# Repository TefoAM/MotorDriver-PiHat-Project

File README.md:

# MotorDriver-PiHat-Project

The PiHAT is a hardware board attached to a Raspberry Pi microcontroller. it is used to drive a motor using an external power source.

##Bill of Materials

- boost convertor.asc
- foldbackcircuit.asc
- main power circuit.asc
- zener.cir
- H-Bridge circuit.asc
- LED Circuit.asc

##Instruction on how to use this repo

This repository contains all the files made using LT Spice and Kicad with which simulations to test the behaviors of the individual circuits were performed.

This git includes a list of documents created during the design of a motor driver PiHAT for a design project.
The software required to use these documents is LT Spice, whcih can be downloaded by following the link below.
https://www.analog.com/en/design-center/design-tools-and-calculators/ltspice-simulator.html# 

The zener.cir file needs to be added into spice as a component to be used. The simulation won't work without it.
Anyone can use these document files except they cannot distribute closed source versions.
- see license.

signed TefoAM

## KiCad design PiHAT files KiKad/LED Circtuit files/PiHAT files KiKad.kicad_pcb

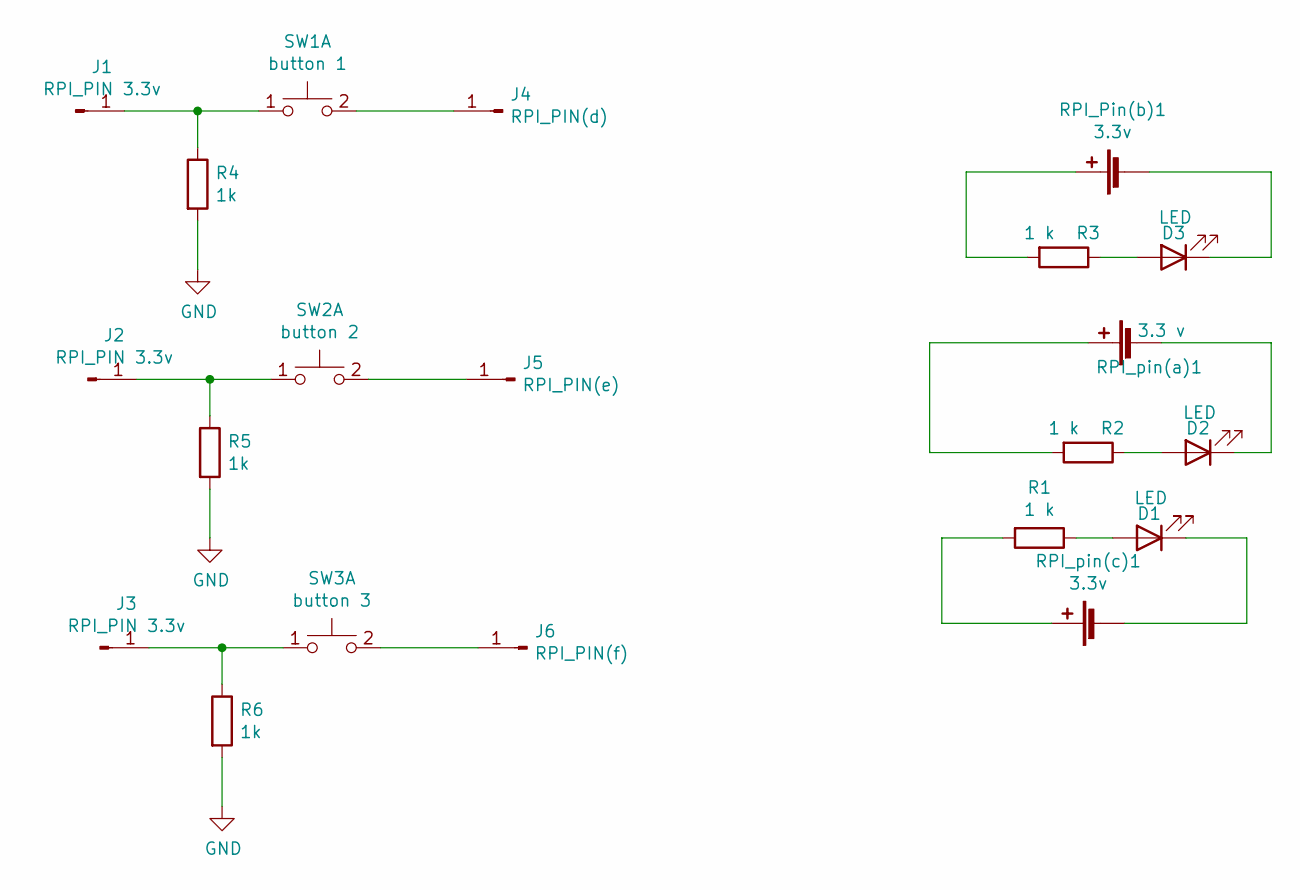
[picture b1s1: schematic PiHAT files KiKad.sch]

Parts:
D1, D2, D3: LED; LED_0603_1608Metric_Pad1.05x0.95mm_HandSolder
J1, J2, J3: RPI_PIN 3.3v; PinHeader_1x01_P2.54mm_Vertical
J4: RPI_PIN(d); PinHeader_1x01_P2.54mm_Vertical
J5: RPI_PIN(e); PinHeader_1x01_P2.54mm_Vertical
J6: RPI_PIN(f); PinHeader_1x01_P2.54mm_Vertical
R1, R2, R3: 1 k; R_0201_0603Metric
R4, R5, R6: 1k; R_0201_0603Metric
RPI_Pin(b)1: 3.3v; PinHeader_1x02_P2.54mm_Vertical
RPI_pin(a)1: 3.3 v; PinHeader_1x02_P2.54mm_Vertical
RPI_pin(c)1: 3.3v; PinHeader_1x02_P2.54mm_Vertical
SW1: button 1; SW_Push_1P1T_NO_6x6mm_H9.5mm
SW2: button 2; SW_Push_1P1T_NO_6x6mm_H9.5mm
SW3: button 3; SW_Push_1P1T_NO_6x6mm_H9.5mm

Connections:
GND: R4.2, R5.2, R6.2
unnamed: D1.1 (K), RPI_pin(c)1.2 (-)
unnamed: D1.2 (A), R1.1
unnamed: D2.1 (K), RPI_pin(a)1.2 (-)
unnamed: D2.2 (A), R2.1
unnamed: D3.1 (K), RPI_Pin(b)1.2 (-)
unnamed: D3.2 (A), R3.1
unnamed: J1.1, R4.1, SW1.1 (C)
unnamed: J2.1, R5.1, SW2.1 (C)
unnamed: J3.1, R6.1, SW3.1 (C)
unnamed: J4.1, SW1.2 (D)
unnamed: J5.1, SW2.2 (D)
unnamed: J6.1, SW3.2 (D)
unnamed: R1.2, RPI_pin(c)1.1 (+)
unnamed: R2.2, RPI_pin(a)1.1 (+)
unnamed: R3.2, RPI_Pin(b)1.1 (+)

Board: 2 copper layers, 21 parts (0 on the bottom side), 16 nets, no tracks yet.

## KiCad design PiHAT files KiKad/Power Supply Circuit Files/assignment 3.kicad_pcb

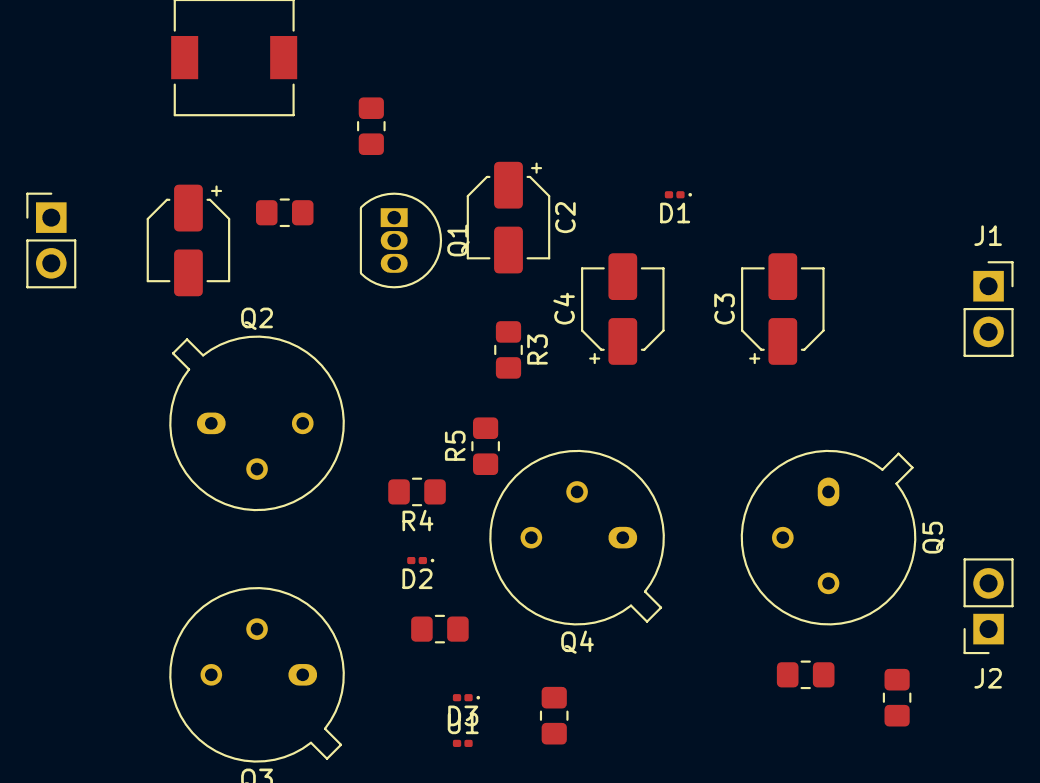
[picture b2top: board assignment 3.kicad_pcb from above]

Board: 4 copper layers, 26 parts (0 on the bottom side), 15 nets, no tracks yet.

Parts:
C1: 10p; CP_Elec_4x3
C2: 0.1u; CP_Elec_4x3
C3: 10u; CP_Elec_4x3
C4: 100u; CP_Elec_4x3
D1, D2, D3: 1N5817; D_0201_0603Metric
J1: Motor_voltage_input; PinSocket_1x02_P2.54mm_Vertical
J2: Controller_input_voltage; PinSocket_1x02_P2.54mm_Vertical
L1: 330u; L_6.3x6.3_H3
Q1: 2N3905; TO-92_Inline
Q2, Q3, Q4, Q5: 2N2219; TO-39-3
R1, R2, R6: 1000; R_0805_2012Metric_Pad1.20x1.40mm_HandSolder
R3: 47000; R_0805_2012Metric_Pad1.20x1.40mm_HandSolder
R4: 470; R_0805_2012Metric_Pad1.20x1.40mm_HandSolder
R5: 4; R_0805_2012Metric_Pad1.20x1.40mm_HandSolder
R7: 5; R_0805_2012Metric_Pad1.20x1.40mm_HandSolder
R8: 100000; R_0805_2012Metric_Pad1.20x1.40mm_HandSolder
R9: 8270; R_0805_2012Metric_Pad1.20x1.40mm_HandSolder
U1: OPAMP; R_0201_0603Metric
power_supply_input1: 12V; PinHeader_1x02_P2.54mm_Vertical

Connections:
GND: C1.2, C3.2, C4.2, D3.1, J1.1, J2.1, Q2.1, R3.2, R5.2, R8.2, power_supply_input1.2
unnamed: C1.1, L1.1, R1.1, power_supply_input1.1
unnamed: C2.1, R2.2
unnamed: C2.2, Q1.2, R3.1
unnamed: C3.1, C4.1, D1.1, D2.1, J1.2, Q4.3, R6.1
unnamed: D1.2, L1.2, Q3.3, R2.1
unnamed: D2.2, Q2.2, R4.2
unnamed: D3.2, R6.2, U1.1
unnamed: J2.2, Q5.3, R7.1, R9.1
unnamed: Q1.1, R1.2
unnamed: Q1.3, Q2.3, Q3.2
unnamed: Q3.1, R4.1, R5.1
unnamed: Q4.1, Q5.2, R7.2
unnamed: Q4.2, Q5.1
unnamed: R8.1, R9.2, U1.2

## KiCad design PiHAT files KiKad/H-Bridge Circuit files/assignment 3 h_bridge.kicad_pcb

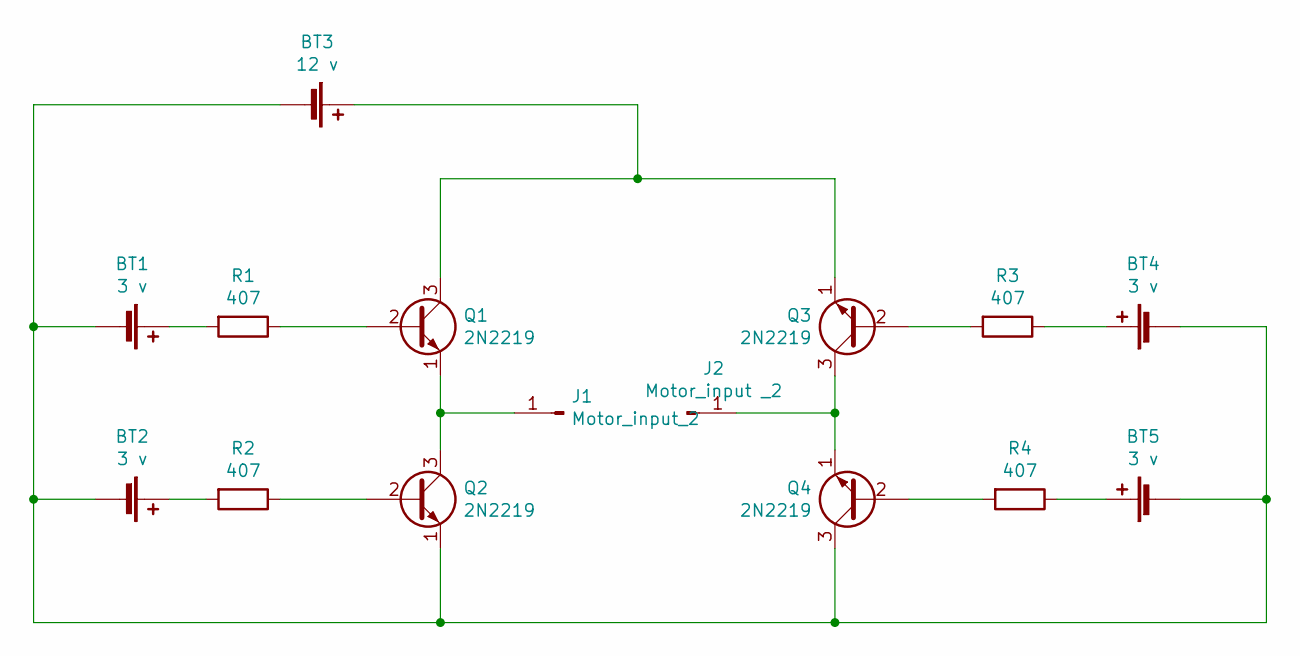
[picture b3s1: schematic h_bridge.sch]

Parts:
BT1, BT2, BT4, BT5: 3 v; PinHeader_1x02_P2.54mm_Vertical
BT3: 12 v; PinHeader_1x02_P2.54mm_Vertical
J1: Motor_input_2; PinSocket_1x01_P2.54mm_Horizontal
J2: Motor_input _2; PinSocket_1x01_P2.54mm_Horizontal
Q1, Q2, Q3, Q4: 2N2219; TO-39-3
R1, R2, R3, R4: 407; R_0201_0603Metric

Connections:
unnamed: BT1.1 (+), R1.2
unnamed: BT1.2 (-), BT2.2 (-), BT3.2 (-), BT4.2 (-), BT5.2 (-), Q2.1 (E), Q4.3 (C)
unnamed: BT2.1 (+), R2.2
unnamed: BT3.1 (+), Q1.3 (C), Q3.1 (E)
unnamed: BT4.1 (+), R3.1
unnamed: BT5.1 (+), R4.1
unnamed: J1.1, Q1.1 (E), Q2.3 (C)
unnamed: J2.1, Q3.3 (C), Q4.1 (E)
unnamed: Q1.2 (B), R1.1
unnamed: Q2.2 (B), R2.1
unnamed: Q3.2 (B), R3.2
unnamed: Q4.2 (B), R4.2

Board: 4 copper layers, 15 parts (0 on the bottom side), 12 nets, no tracks yet.

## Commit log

2021-05-13 HandIn 2 Spice files with which simulations were made.
2021-05-13 Update README.md file.
    Added the following points to make the readme file more comprehensive.
    I. What’s here
    II. How to install it
    III. How to use it
    IV. An example of using it
    V. Usage rights
2021-05-13 one file i forgot to add while committing others.
2021-05-13 added a readme file with just the description of what the circuit is doing.
2021-05-13 added a license file.
2021-05-13 added a bill of materials and how to use the repo.
2021-05-13 tried to style the readme file.
2021-06-02 Kicad files added to the project
2021-06-04 LED, H-bridge and Power Circuit Kicad files separated.
2021-06-04 initial kicad files removed from the git.
2021-06-04 Added folder for the PCB.
2021-06-15 just added a few more words to the repo.
